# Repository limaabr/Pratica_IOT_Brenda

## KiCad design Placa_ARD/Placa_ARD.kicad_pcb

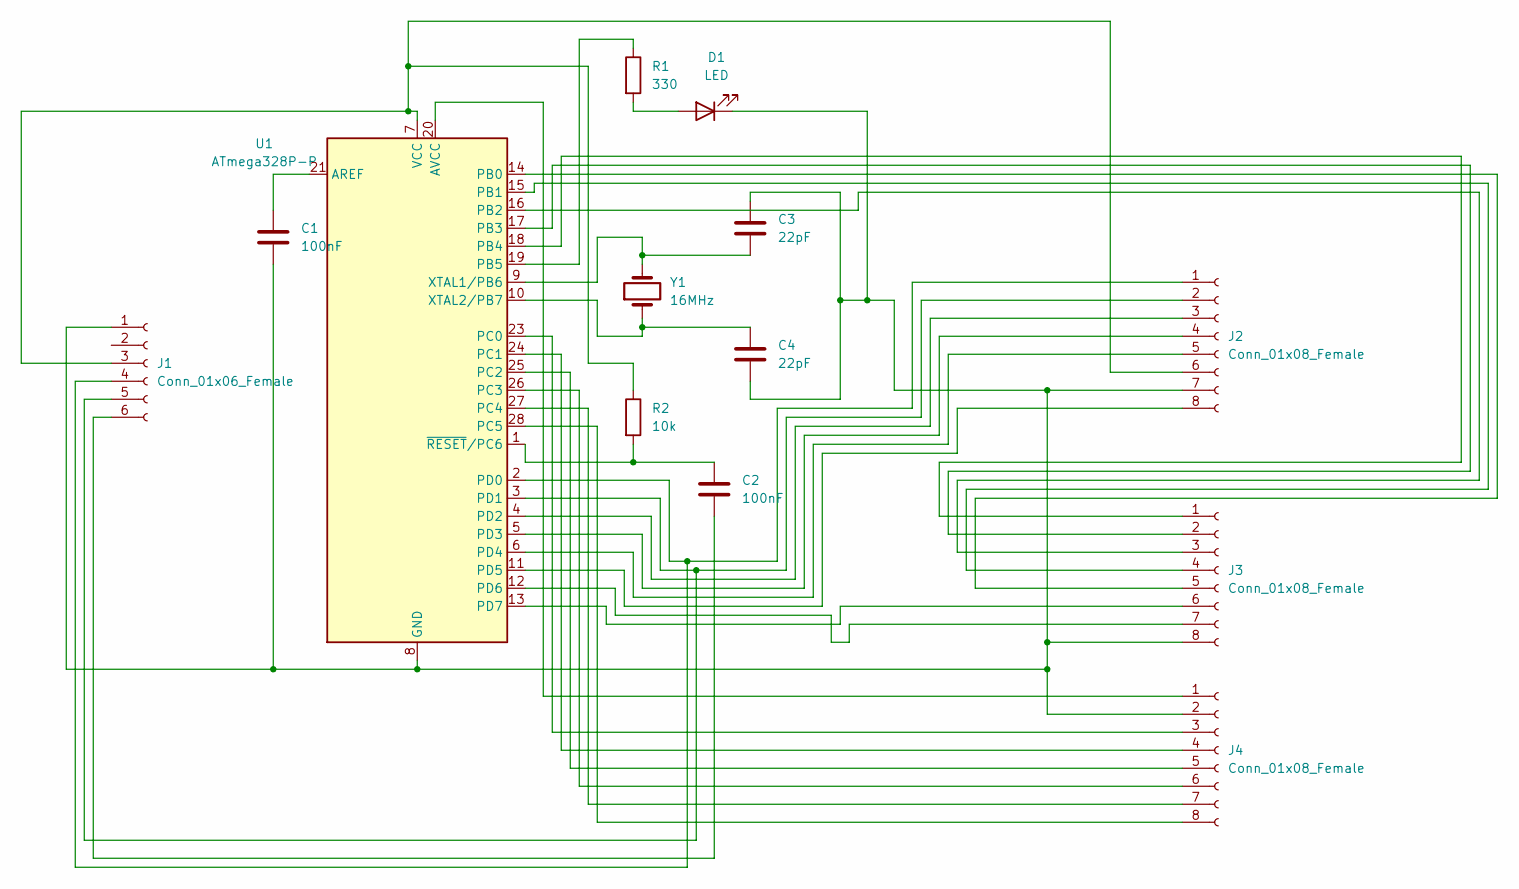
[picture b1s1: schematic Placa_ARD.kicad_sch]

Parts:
C1: 100nF; C_Disc_D5.0mm_W2.5mm_P5.00mm
C2: 100nF; C_Disc_D3.0mm_W1.6mm_P2.50mm
C3, C4: 22pF; C_Disc_D3.0mm_W1.6mm_P2.50mm
D1: LED; LED_D3.0mm
J1: Conn_01x06_Female; PinSocket_1x06_P2.54mm_Vertical
J2, J3, J4: Conn_01x08_Female; PinSocket_1x08_P2.54mm_Vertical
R1: 330; R_Axial_DIN0204_L3.6mm_D1.6mm_P7.62mm_Horizontal
R2: 10k; R_Axial_DIN0204_L3.6mm_D1.6mm_P7.62mm_Horizontal
U1: ATmega328P-P; DIP-28_W7.62mm
Y1: 16MHz; Crystal_HC49-4H_Vertical

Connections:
unnamed: C2.2, J1.6
unnamed: D1.2 (A), R1.2
unnamed: J1.3, J2.6, R2.1, U1.7 (VCC)
unnamed: C2.1, R2.2, U1.1 (~RESET/PC6)
unnamed: J1.4, J2.1, U1.2 (PD0)
unnamed: J1.5, J2.2, U1.3 (PD1)
unnamed: J2.3, U1.4 (PD2)
unnamed: J2.4, U1.5 (PD3)
unnamed: J2.5, U1.6 (PD4)
unnamed: C3.2, U1.9 (XTAL1/PB6), Y1.2
unnamed: C4.1, U1.10 (XTAL2/PB7), Y1.1
unnamed: J2.8, U1.11 (PD5)
unnamed: J3.7, U1.12 (PD6)
unnamed: J3.6, U1.13 (PD7)
unnamed: J3.5, U1.14 (PB0)
unnamed: J3.4, U1.15 (PB1)
unnamed: J3.3, U1.16 (PB2)
unnamed: J3.2, U1.17 (PB3)
unnamed: J3.1, U1.18 (PB4)
unnamed: R1.1, U1.19 (PB5)
unnamed: J4.1, U1.20 (AVCC)
unnamed: C1.1, U1.21 (AREF)
unnamed: C1.2, C3.1, C4.2, D1.1 (K), J1.1, J2.7, J3.8, J4.2, U1.8 (GND), U1.22 (GND)
unnamed: J4.3, U1.23 (PC0)
unnamed: J4.4, U1.24 (PC1)
unnamed: J4.5, U1.25 (PC2)
unnamed: J4.6, U1.26 (PC3)
unnamed: J4.7, U1.27 (PC4)
unnamed: J4.8, U1.28 (PC5)

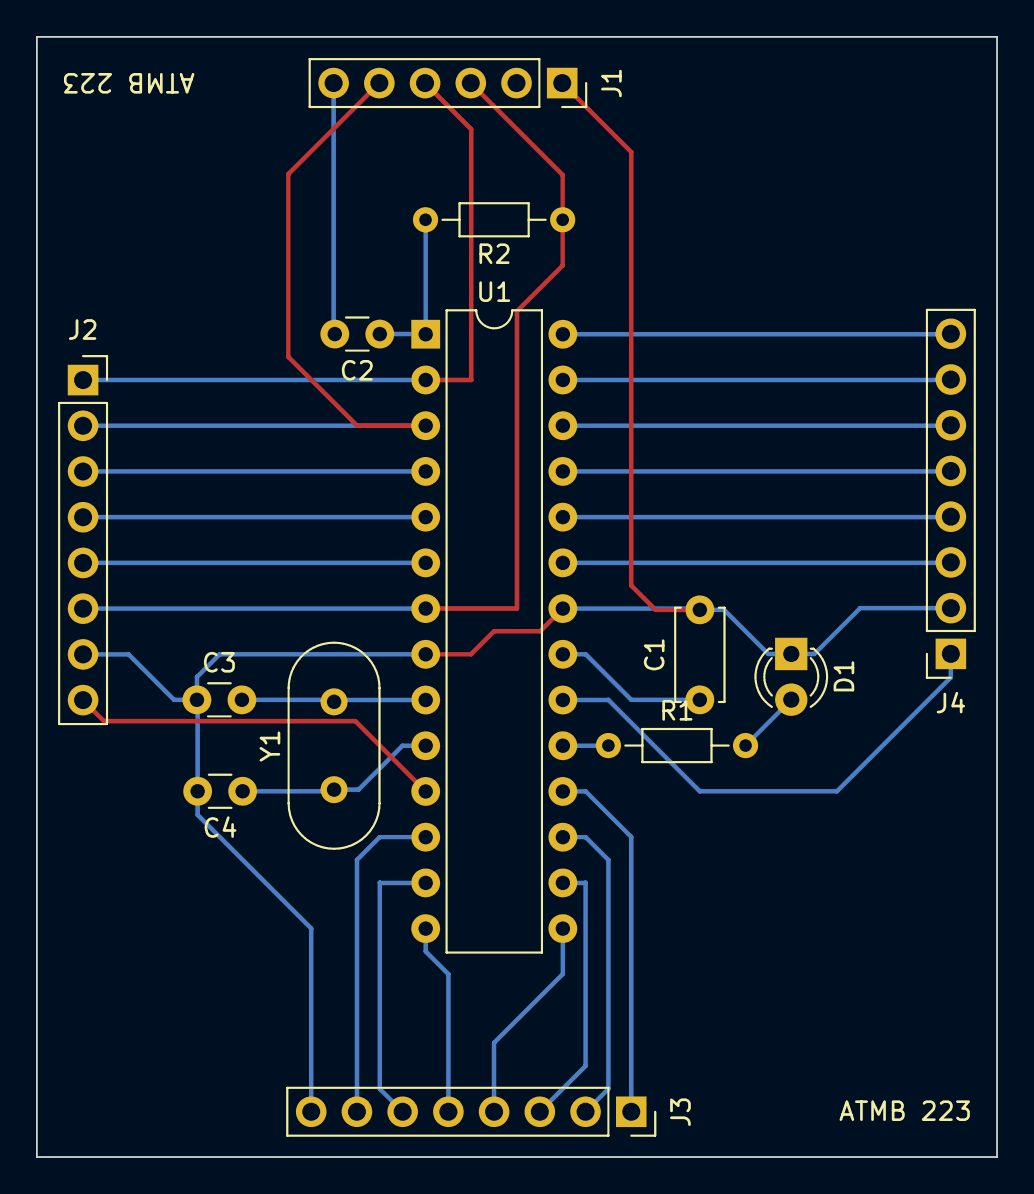
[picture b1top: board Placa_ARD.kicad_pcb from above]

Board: 2 copper layers, 53.3 x 62.2 mm, 13 parts (0 on the bottom side), 29 nets.

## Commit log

2024-03-29 fist commit
2024-04-23 fotos placa ARD
